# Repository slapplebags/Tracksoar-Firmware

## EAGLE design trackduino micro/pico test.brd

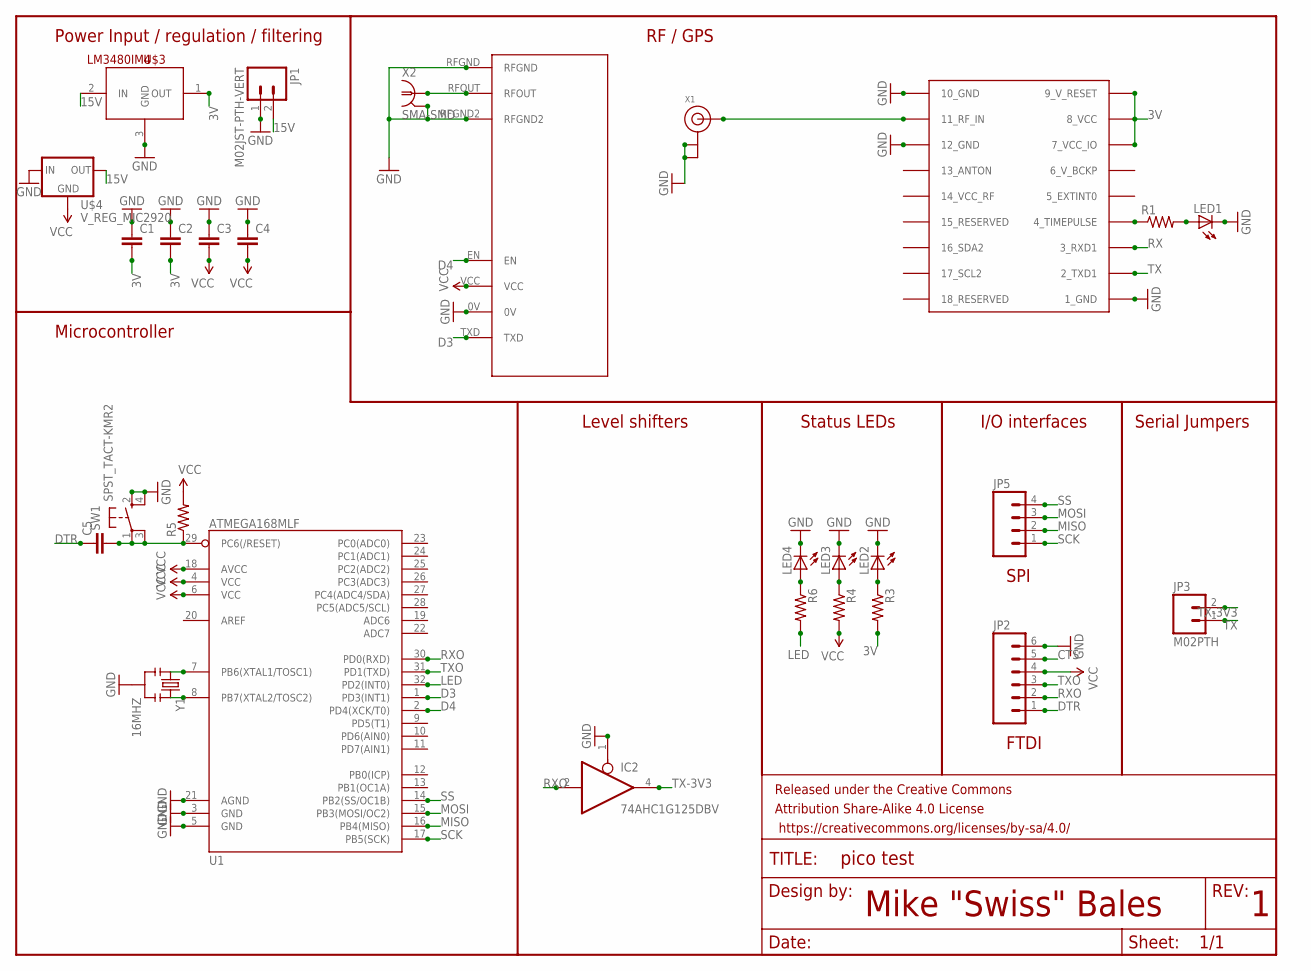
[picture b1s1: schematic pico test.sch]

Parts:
C1, C2, C3, C4, C5: CAP0805; 0805
FRAME1: FRAME-LETTER; CREATIVE_COMMONS
IC2: 74AHC1G125DBV; SOT23-5
JP1: M02JST-PTH-VERT; JST-2-PTH-VERT
JP2: M06NO_SILK_FEMALE_PTH; 1X06_NO_SILK
JP3: M02PTH; 1X02
JP5: M041X04_NO_SILK; 1X04_NO_SILK
LED1, LED2, LED3, LED4: LEDCHIP-LED0805; CHIP-LED0805
R1, R3, R4, R5, R6: RESISTOR0805-RES; 0805
SW1: SPST_TACT-KMR2; KMR2
U1: ATMEGA168MLF; MLF32
U$1: UBLOX_MAX
U$2: RADIOMETRIX-HX1
U$3: LM3480IM4; SOT23-3
U$4: V_REG_MIC2920; SOT223
X1: ANTENNA_U.FL; U.FL
X2: SMA-SMD
Y1: 16MHZ; RESONATOR-SMD

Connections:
3V: C1.2, C2.2, R3.2, U$1.7_VCC_IO, U$1.8_VCC, U$1.9_V_RESET, U$3.1 (OUT)
15V: JP1.2, U$3.2 (IN), U$4.3 (OUT)
CTS: JP2.5
D3: U1.1 (PD3(INT1)), U$2.TXD
D4: U1.2 (PD4(XCK/T0)), U$2.EN
DTR: C5.1, JP2.1
GND: C1.1, C2.1, C3.1, C4.1, IC2.1 (OE), IC2.3 (GND), JP1.1, JP2.6, LED1.C, LED2.C, LED3.C, LED4.C, SW1.2 (S), SW1.4 (S1), U1.3 (GND), U1.5 (GND), U1.21 (AGND), U$1.1_GND, U$1.10_GND, U$1.12_GND, U$2.0V, U$2.RFGND, U$2.RFGND2, U$3.3 (GND), U$4.1 (IN), X1.1 (GND), X1.2 (GND), X2.2@1 (2), X2.2@2 (2), X2.2@3 (2), X2.2@4 (2), X2.2@5 (2), X2.2@6 (2), Y1.2
LED: R6.2, U1.32 (PD2(INT0))
MISO: JP5.2, U1.16 (PB4(MISO))
MOSI: JP5.3, U1.15 (PB3(MOSI/OC2))
unnamed: U$2.RFOUT, X2.1
unnamed: R1.1, U$1.4_TIMEPULSE
unnamed: LED1.A, R1.2
unnamed: U$1.11_RF_IN, X1.3 (SIGNAL)
unnamed: LED2.A, R3.1
unnamed: LED3.A, R4.1
unnamed: C5.2, R5.1, SW1.1, SW1.3 (P1), U1.29 (PC6(/RESET))
unnamed: U1.8 (PB7(XTAL2/TOSC2)), Y1.3
unnamed: U1.7 (PB6(XTAL1/TOSC1)), Y1.1
unnamed: LED4.A, R6.1
RX: U$1.3_RXD1
RXO: IC2.2 (I), JP2.2, U1.30 (PD0(RXD))
SCK: JP5.1, U1.17 (PB5(SCK))
SS: JP5.4, U1.14 (PB2(SS/OC1B))
TX: JP3.1, U$1.2_TXD1
TX-3V3: IC2.4 (O), JP3.2
TXO: JP2.3, U1.31 (PD1(TXD))
VCC: C3.2, C4.2, IC2.5 (VCC), JP2.4, R4.2, R5.2, U1.4 (VCC), U1.6 (VCC), U1.18 (AVCC), U$2.VCC, U$4.2 (GND)

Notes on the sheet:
Mike "Swiss" Bales
Power Input / regulation / filtering
RF / GPS
Microcontroller
Level shifters
Status LEDs
I/O interfaces
Serial Jumpers
SPI
FTDI

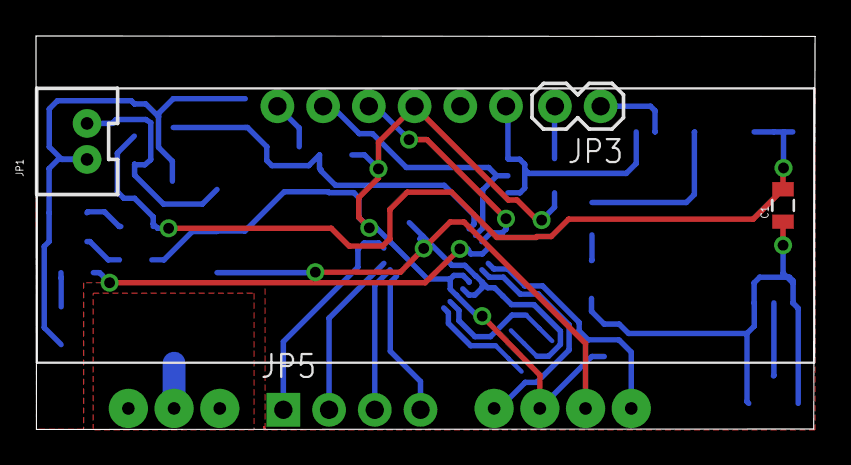
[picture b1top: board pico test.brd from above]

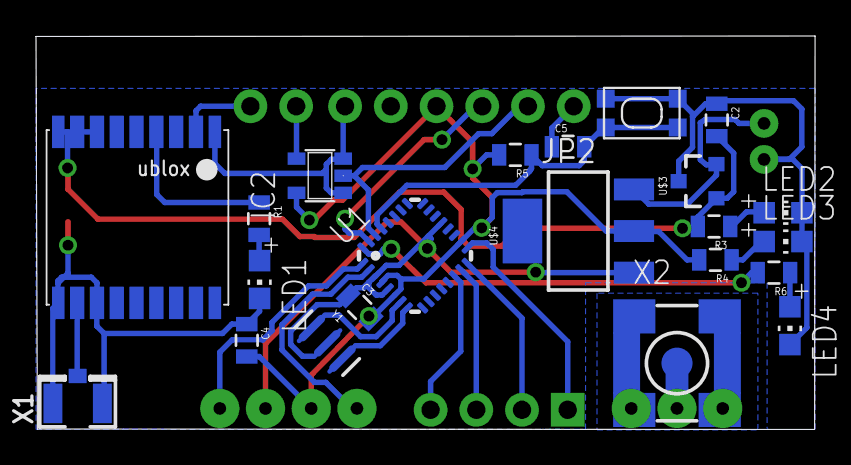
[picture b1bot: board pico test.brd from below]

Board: 2 copper layers, 43.3 x 21.9 mm, 29 parts (23 on the bottom side), 26 nets.

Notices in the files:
parts and their libraries:
SparkFun-PowerIC: Licensing: Creative Commons ShareAlike 4.0 International - https://creativecommons.org/licenses/by-sa/4.0
SparkFun-Aesthetics: Released under the Creative Commons Attribution Share-Alike 4.0 License
SparkFun-Aesthetics: https://creativecommons.org/licenses/by-sa/4.0
